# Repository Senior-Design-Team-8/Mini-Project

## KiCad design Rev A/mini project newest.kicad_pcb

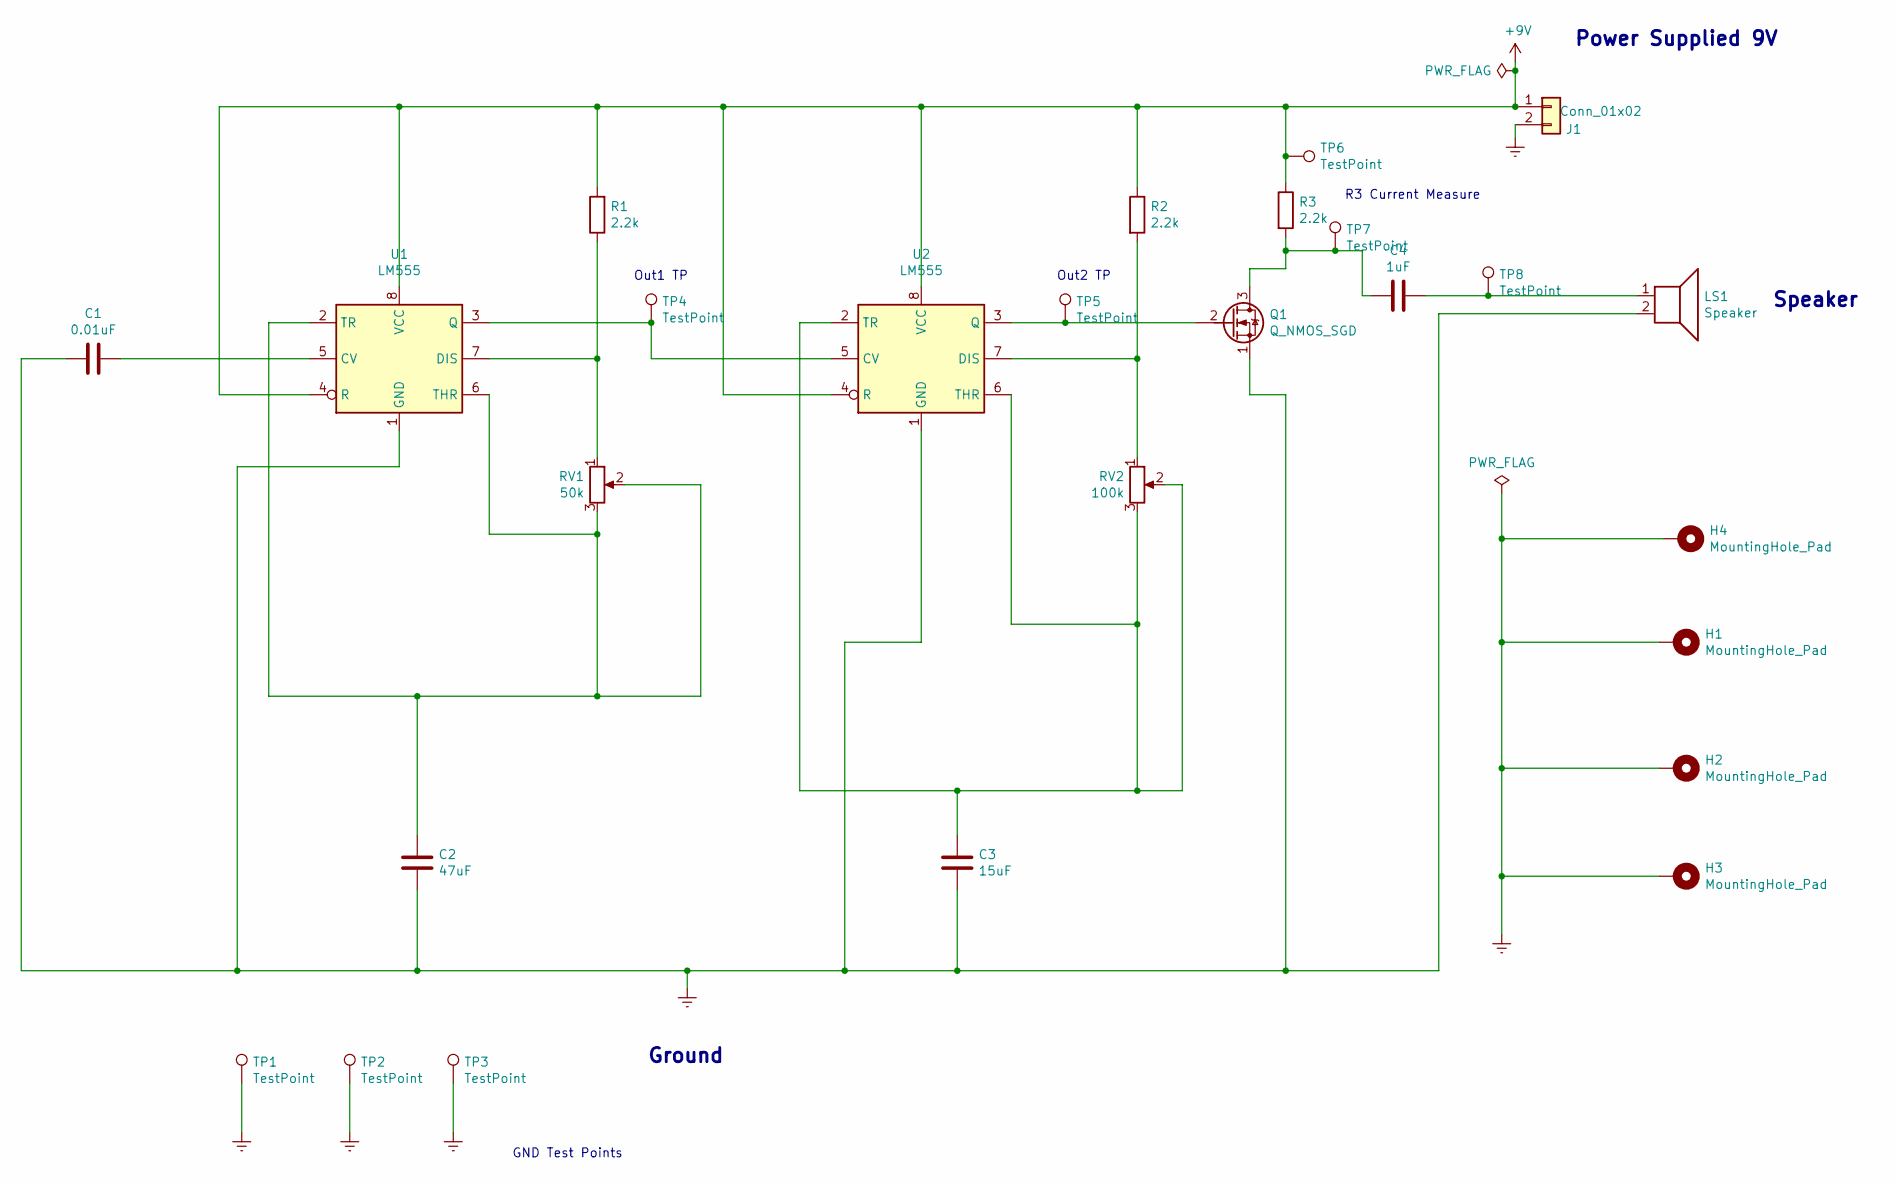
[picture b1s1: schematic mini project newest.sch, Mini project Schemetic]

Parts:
C1: 0.01uF; C_Disc_D3.0mm_W2.0mm_P2.50mm
C2: 47uF; C_Disc_D3.0mm_W2.0mm_P2.50mm
C3: 15uF; C_Disc_D3.0mm_W2.0mm_P2.50mm
C4: 1uF; C_Disc_D3.0mm_W2.0mm_P2.50mm
H1, H2, H3, H4: MountingHole_Pad; MountingHole_2.7mm_M2.5_Pad
J1: Conn_01x02; PinHeader_1x02_P1.00mm_Vertical
LS1: Speaker; PinHeader_1x02_P2.00mm_Vertical
Q1: Q_NMOS_SGD; TO-92
R1, R2, R3: 2.2k; R_Axial_DIN0207_L6.3mm_D2.5mm_P10.16mm_Horizontal
RV1: 50k; Potentiometer_ACP_CA9-H5_Horizontal
RV2: 100k; Potentiometer_ACP_CA9-H5_Horizontal
TP1, TP2, TP3, TP4, TP5, TP6, TP7, TP8: TestPoint; PinHeader_1x01_P1.00mm_Vertical
U1, U2: LM555; DIP-8_W7.62mm

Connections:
+9V: J1.1, R1.2, R2.1, R3.1, TP6.1, U1.4 (R), U1.8 (VCC), U2.4 (R), U2.8 (VCC)
Earth: C1.2, C2.2, C3.2, H1.1, H2.1, H3.1, H4.1, J1.2, LS1.2, Q1.1 (S), TP1.1, TP2.1, TP3.1, U1.1 (GND), U2.1 (GND)
unnamed: C1.1, U1.5 (CV)
unnamed: C2.1, RV1.2, RV1.3, U1.2 (TR), U1.6 (THR)
unnamed: C3.1, RV2.2, RV2.3, U2.2 (TR), U2.6 (THR)
unnamed: C4.1, LS1.1, TP8.1
unnamed: C4.2, Q1.3 (D), R3.2, TP7.1
unnamed: Q1.2 (G), TP5.1, U2.3 (Q)
unnamed: R1.1, RV1.1, U1.7 (DIS)
unnamed: R2.2, RV2.1, U2.7 (DIS)
unnamed: TP4.1, U1.3 (Q), U2.5 (CV)

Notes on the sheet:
Power Supplied 9V
Ground
Speaker
GND Test Points
Out1 TP
Out2 TP
R3 Current Measure

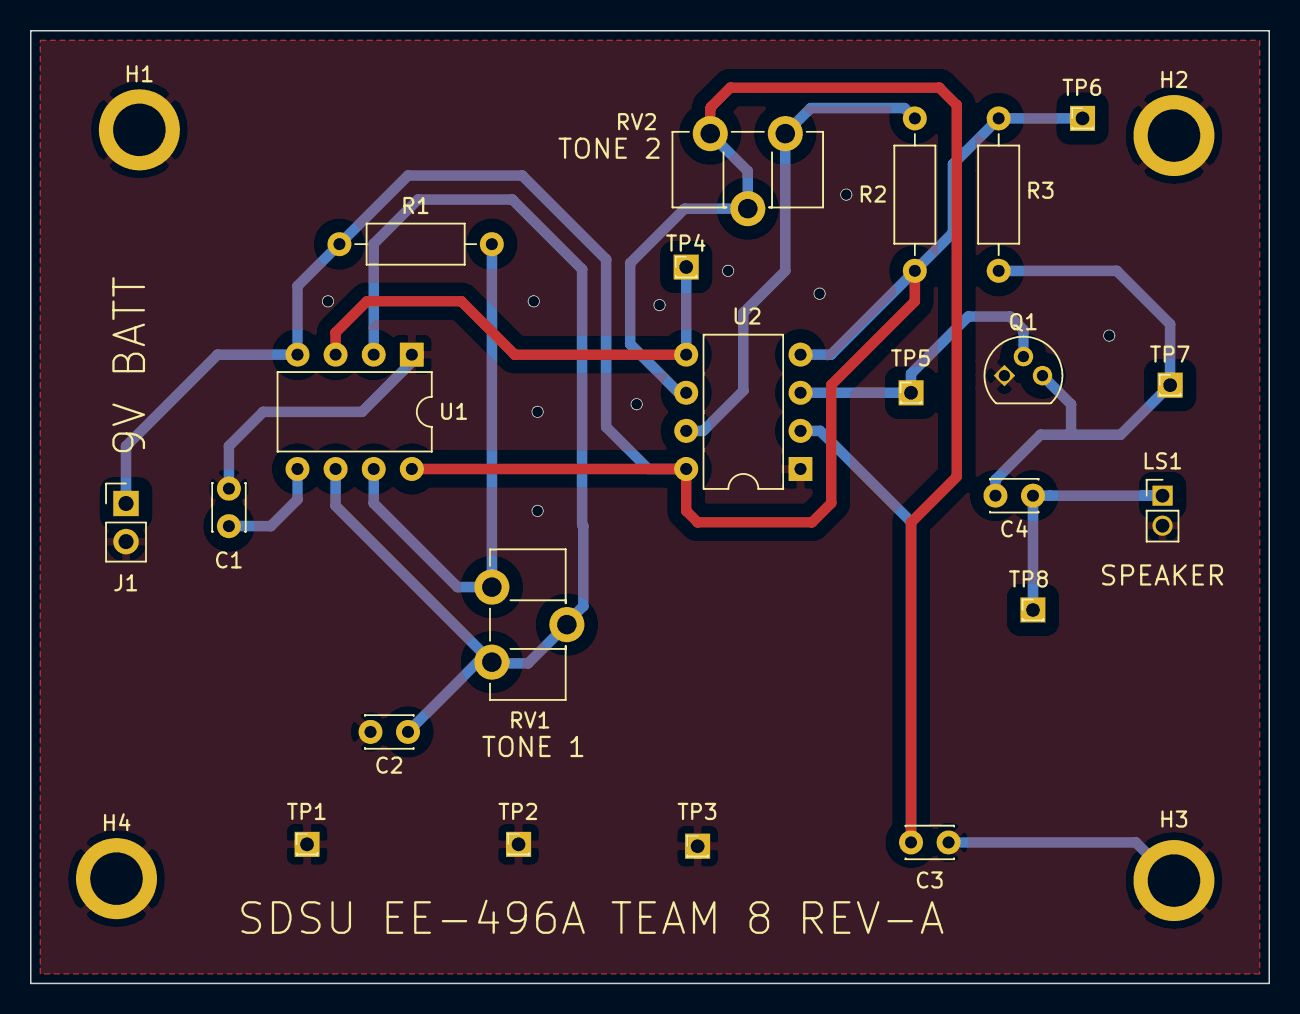
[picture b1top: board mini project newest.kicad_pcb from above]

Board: 2 copper layers, 82.6 x 63.5 mm, 26 parts (0 on the bottom side), 11 nets.

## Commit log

2020-09-20 added mini project BOM and Proposal
2020-09-29 Rev A of mini PCB
2020-10-02 updated the BOM with new compoents 555 timer and mosfet
2020-10-02 updated 555 timer and mosfet footprints from smd to through-hole. Layout needs to be updated
2020-10-02 new foot prints, new traces, new coat of paint. a few errors still need to be worked out, mostly with footprints not playing well with thicc traces
2020-10-02 fixed mosfet footprint, made vias bigger, going to clean up traces
2020-10-03 shortened some traces, theres a problem with the ground pin for power
2020-10-03 Fixed traces not grounding properly, fixed pad too close to pad bugs, finished silkscreen, changed mounting hole sizes, repositioned TPs
2020-10-03 changed pin sizes for test point and speaker pins per Mark Bruno's suggestion. He cant mill the tiny holes we had. He also suggested chaning the POT footprints if we wanted to use the schools POTs bu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
